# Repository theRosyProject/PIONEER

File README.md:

# PIONEER
Marie Skłodowska-Curie grant agreement No. 844526 

https://cordis.europa.eu/project/id/844526

## Publications
Dallo, Federico, et al. "Calibration and assessment of electrochemical low-cost sensors in remote alpine harsh environments." Atmospheric Measurement Techniques 14.9 (2021): 6005-6021. https://doi.org/10.5194/amt-14-6005-2021

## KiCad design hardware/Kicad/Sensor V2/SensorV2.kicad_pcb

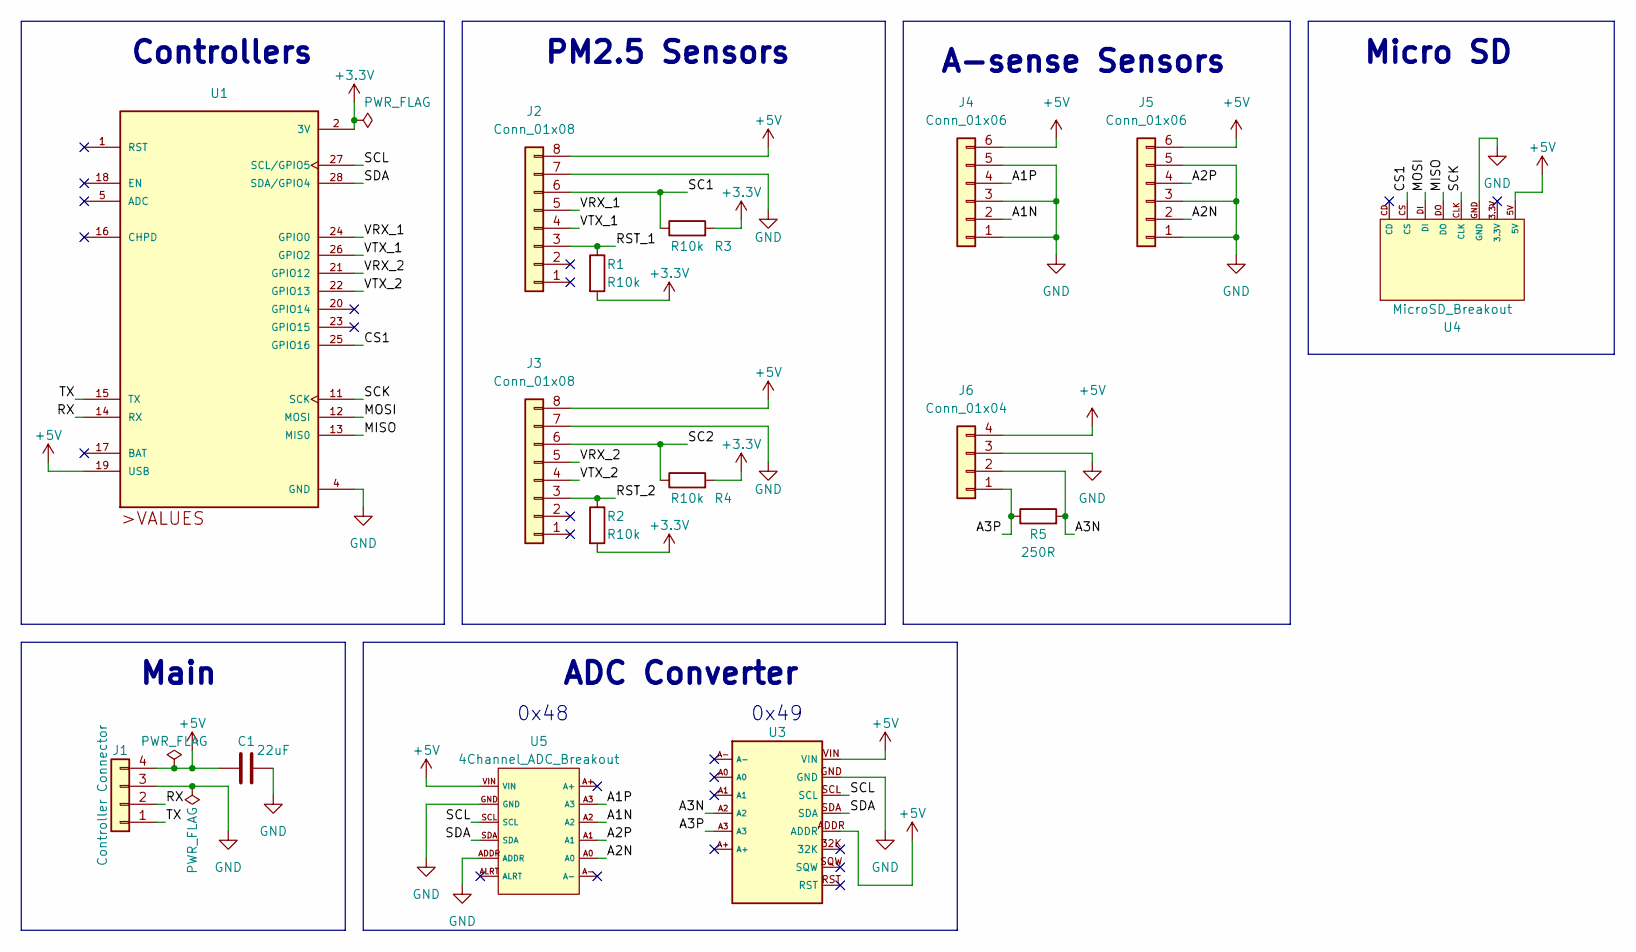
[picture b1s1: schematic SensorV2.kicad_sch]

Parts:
C1: 22uF; C_1206_3216Metric
J1: Controller Connector; PinHeader_1x04_P2.54mm_Vertical
J2, J3: Conn_01x08; Molex_CLIK-Mate_502386-0870_1x08-1MP_P1.25mm_Horizontal
J4, J5: Conn_01x06; JST_XH_B6B-XH-A_1x06_P2.50mm_Vertical
J6: Conn_01x04; JST_XH_B4B-XH-AM_1x04_P2.50mm_Vertical
R1, R2, R3, R4: R10k; R_1206_3216Metric
R5: 250R; R_0805_2012Metric
U1: 2821; XCVR_Adafruit Feather ESP8266
U3: ADCRTC_Dual
U4: MicroSD_Breakout
U5: 4Channel_ADC_Breakout; 4Channel ADC Breakout

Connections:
+3V3: R1.2, R2.2, R3.2, R4.2, U1.2 (3V)
+5V: C1.1, J1.4, J2.8, J3.8, J4.6, J5.6, J6.4, U1.19 (USB), U3.ADDR, U3.VIN, U4.5V, U5.VIN
/A1N: J4.2, U5.A2
/A1P: J4.4, U5.A3
/A2N: J5.2, U5.A0
/A2P: J5.4, U5.A1
/A3N: J6.2, R5.2, U3.A2
/A3P: J6.1, R5.1, U3.A3
/CS1: U1.25 (GPIO16), U4.CS
/MISO: U1.13 (MIS0), U4.DO
/MOSI: U1.12 (MOSI), U4.DI
/RST_1: J2.3, R1.1
/RST_2: J3.3, R2.1
/RX: J1.2, U1.14 (RX)
/SC1: J2.6, R3.1
/SC2: J3.6, R4.1
/SCK: U1.11 (SCK), U4.CLK
/SCL: U1.27 (SCL/GPIO5), U3.SCL, U5.SCL
/SDA: U1.28 (SDA/GPIO4), U3.SDA, U5.SDA
/TX: J1.1, U1.15 (TX)
/VRX_1: J2.5, U1.24 (GPIO0)
/VRX_2: J3.5, U1.21 (GPIO12)
/VTX_1: J2.4, U1.26 (GPIO2)
/VTX_2: J3.4, U1.22 (GPIO13)
GND: C1.2, J1.3, J2.7, J3.7, J4.1, J4.3, J4.5, J5.1, J5.3, J5.5, J6.3, U1.4 (GND), U3.GND, U4.GND, U5.ADDR, U5.GND

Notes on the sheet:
Controllers
ADC Converter
0x49
A-sense Sensors
Micro SD
Main
0x48
PM2.5 Sensors

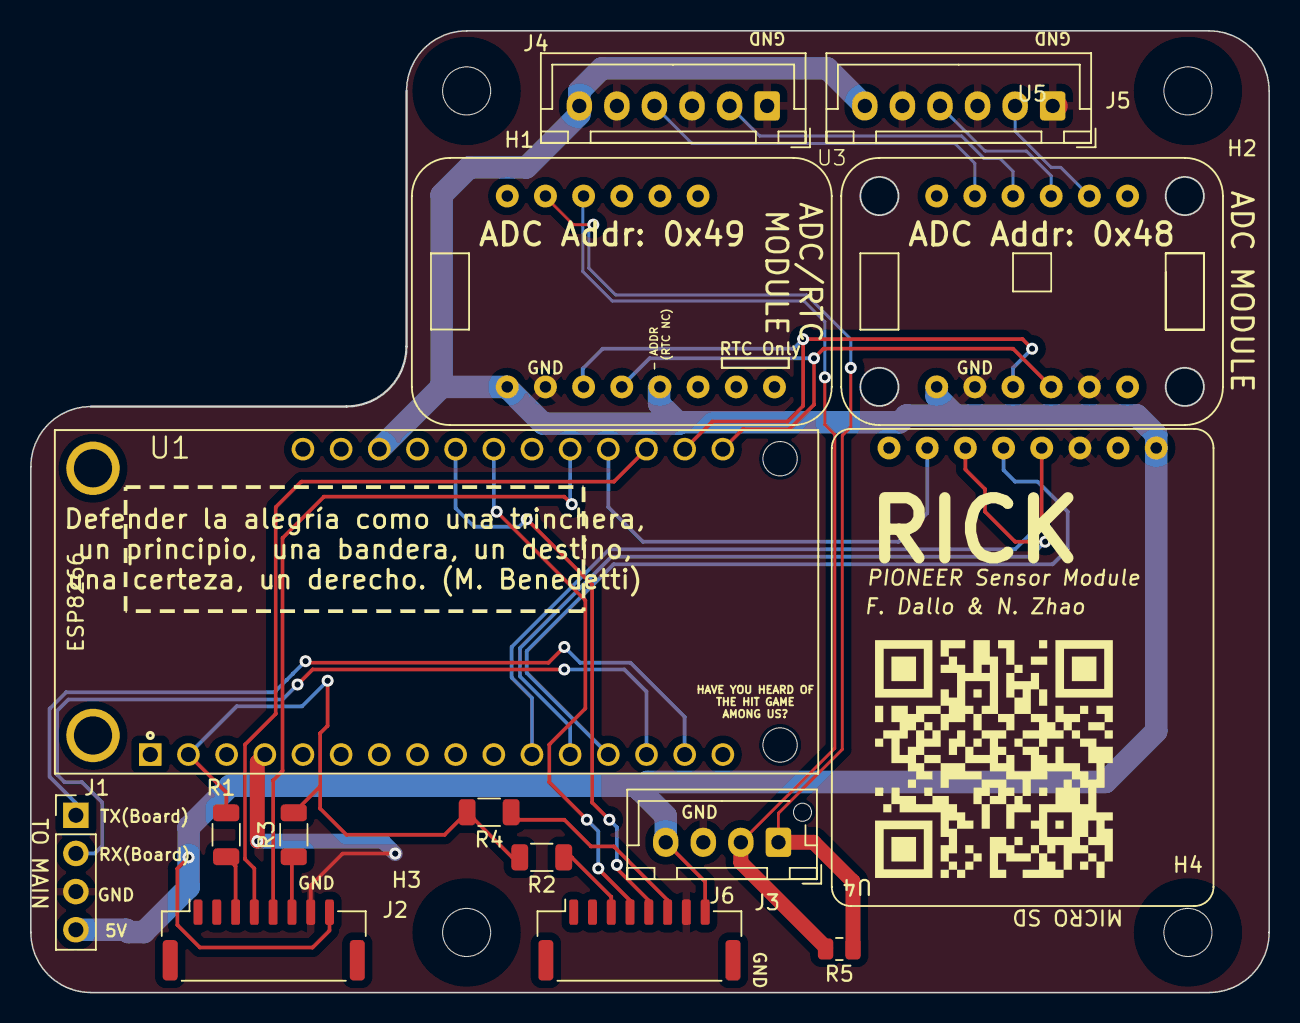
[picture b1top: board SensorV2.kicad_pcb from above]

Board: 2 copper layers, 82.4 x 64.0 mm, 20 parts (1 on the bottom side), 25 nets.

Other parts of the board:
H1, H2, H3, H4: MountingHole_3.2mm_M3

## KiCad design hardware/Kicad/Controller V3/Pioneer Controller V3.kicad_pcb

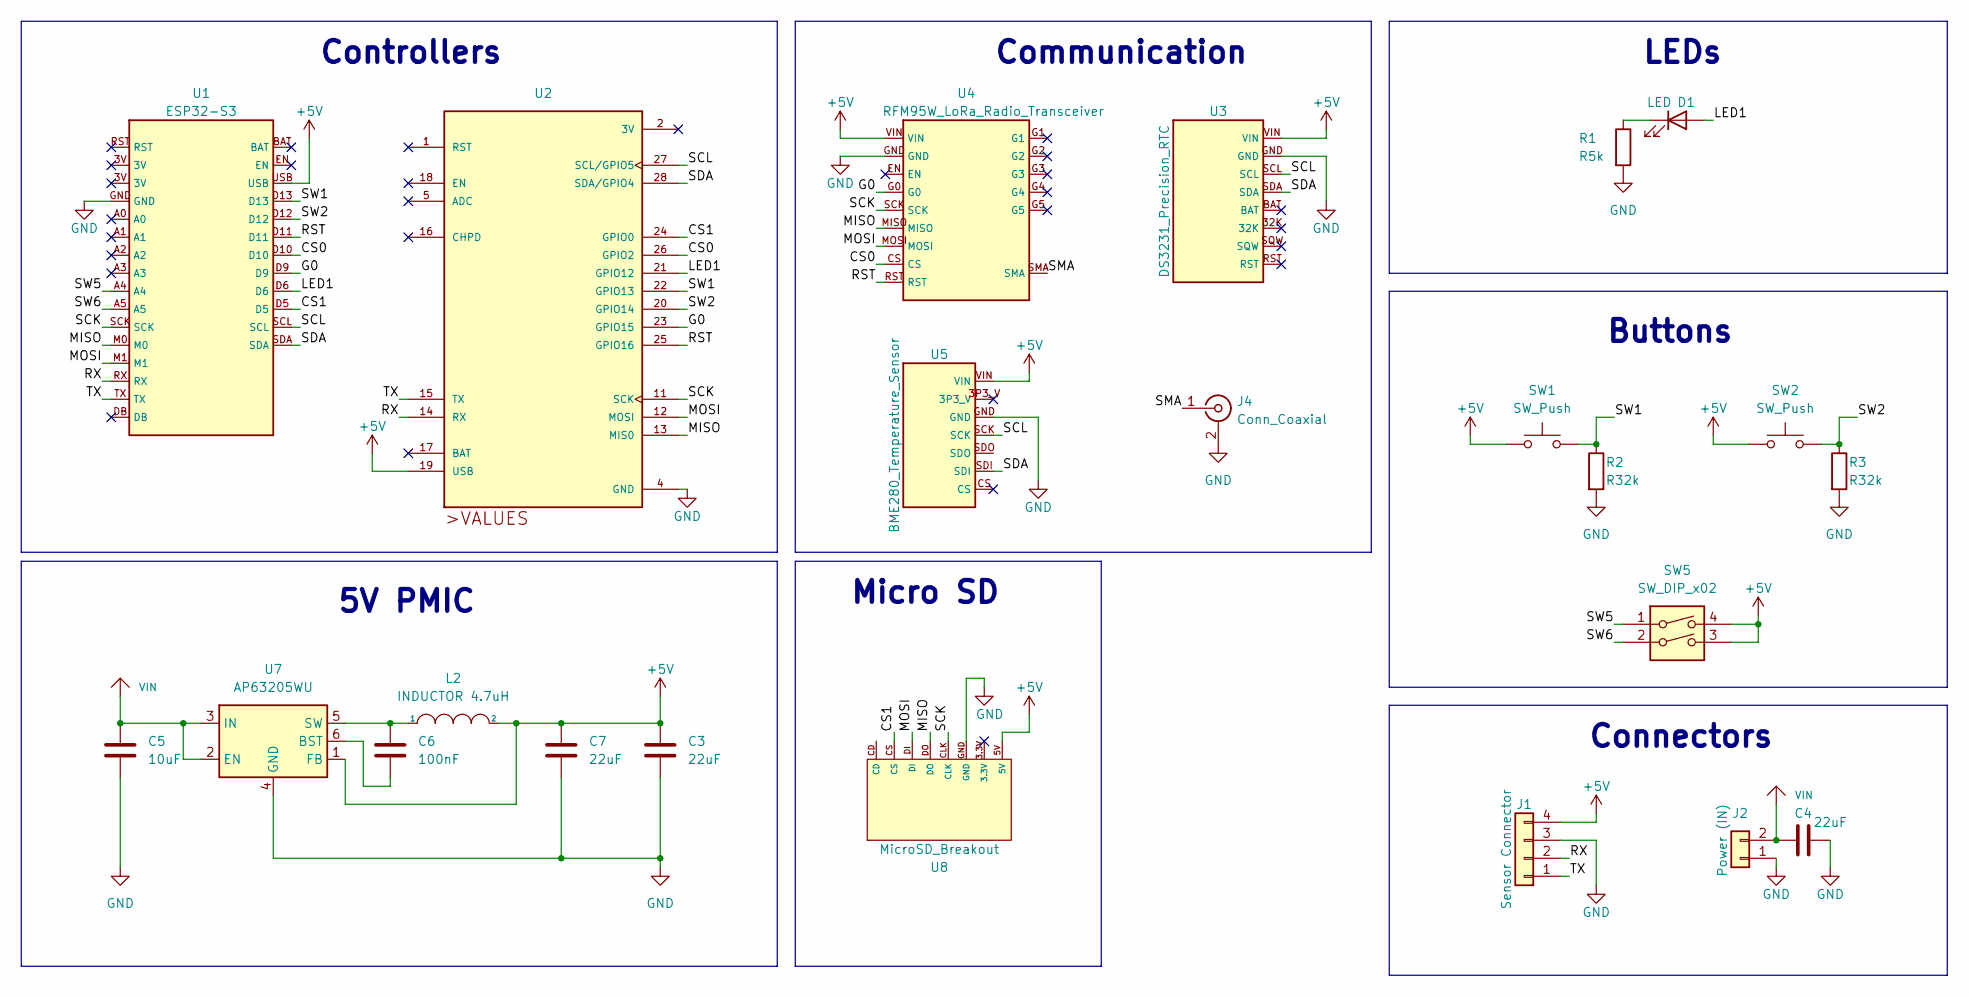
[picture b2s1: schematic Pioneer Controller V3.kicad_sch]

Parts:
C3, C4, C7: 22uF; C_1206_3216Metric
C5: 10uF; C_1206_3216Metric
C6: 100nF; C_1206_3216Metric
D1: LED; LED_1206_3216Metric
J1: Sensor Connector; PinHeader_1x04_P2.54mm_Vertical
J2: Power (IN); PinHeader_1x02_P2.54mm_Vertical
J4: Conn_Coaxial; SMA_Amphenol_132134-11_Vertical
L2: INDUCTOR 4.7uH; L_1206_3216Metric
R1: R5k; R_1206_3216Metric
R2, R3: R32k; R_1206_3216Metric
SW1, SW2: SW_Push; SW_PUSH_6mm
SW5: SW_DIP_x02; SW_DIP_SPSTx02_Slide_9.78x7.26mm_W7.62mm_P2.54mm
U1: ESP32-S3
U2: 2821; XCVR_Adafruit Feather ESP8266
U3: DS3231_Precision_RTC; DS3231 Precision RTC
U4: RFM95W_LoRa_Radio_Transceiver; FM95W LoRa Radio Transceiver
U5: BME280_Temperature_Sensor; BME280 I2C Temperature Sensor
U7: AP63205WU; TSOT-23-6
U8: MicroSD_Breakout

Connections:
+5V: C3.1, C7.1, J1.4, L2.2, SW1.1, SW2.1, SW5.3, SW5.4, U1.USB, U2.19 (USB), U3.VIN, U4.VIN, U5.VIN, U7.1 (FB), U8.5V
/CS0: U1.D10, U2.26 (GPIO2), U4.CS
/CS1: U1.D5, U2.24 (GPIO0), U8.CS
/G0: U1.D9, U2.23 (GPIO15), U4.G0
/LED1: D1.2 (A), U1.D6, U2.21 (GPIO12)
/MISO: U1.M0, U2.13 (MIS0), U4.MISO, U8.DO
/MOSI: U1.M1, U2.12 (MOSI), U4.MOSI, U8.DI
/RST: U1.D11, U2.25 (GPIO16), U4.RST
/RX: J1.2, U1.RX, U2.14 (RX)
/SCK: U1.SCK, U2.11 (SCK), U4.SCK, U8.CLK
/SCL: U1.SCL, U2.27 (SCL/GPIO5), U3.SCL, U5.SCK
/SDA: U1.SDA, U2.28 (SDA/GPIO4), U3.SDA, U5.SDI
/SMA: J4.1 (In), U4.SMA
/SW1: R2.1, SW1.2, U1.D13, U2.22 (GPIO13)
/SW2: R3.1, SW2.2, U1.D12, U2.20 (GPIO14)
/SW5: SW5.1, U1.A4
/SW6: SW5.2, U1.A5
/TX: J1.1, U1.TX, U2.15 (TX)
GND: C3.2, C4.2, C5.2, C7.2, J1.3, J2.1, J4.2 (Ext), R1.2, R2.2, R3.2, U1.GND, U2.4 (GND), U3.GND, U4.GND, U5.GND, U7.4 (GND), U8.GND
unnamed: D1.1 (K), R1.1
unnamed: C6.2, U7.6 (BST)
unnamed: C6.1, L2.1, U7.5 (SW)
VIN: C4.1, C5.1, J2.2, U7.2 (EN), U7.3 (IN)

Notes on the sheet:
Communication
Controllers
Connectors
Buttons
Micro SD
LEDs
5V PMIC

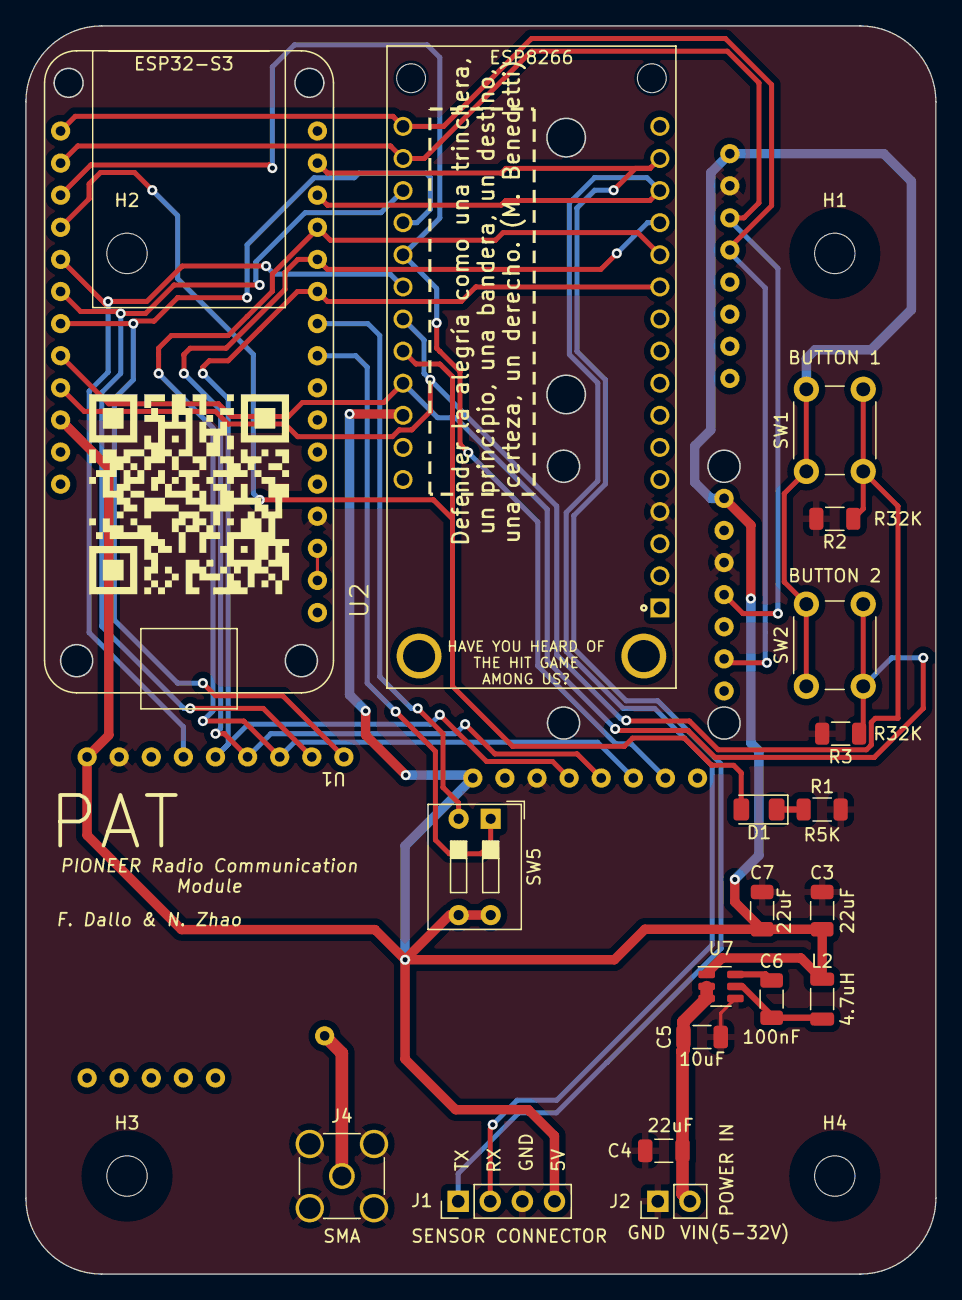
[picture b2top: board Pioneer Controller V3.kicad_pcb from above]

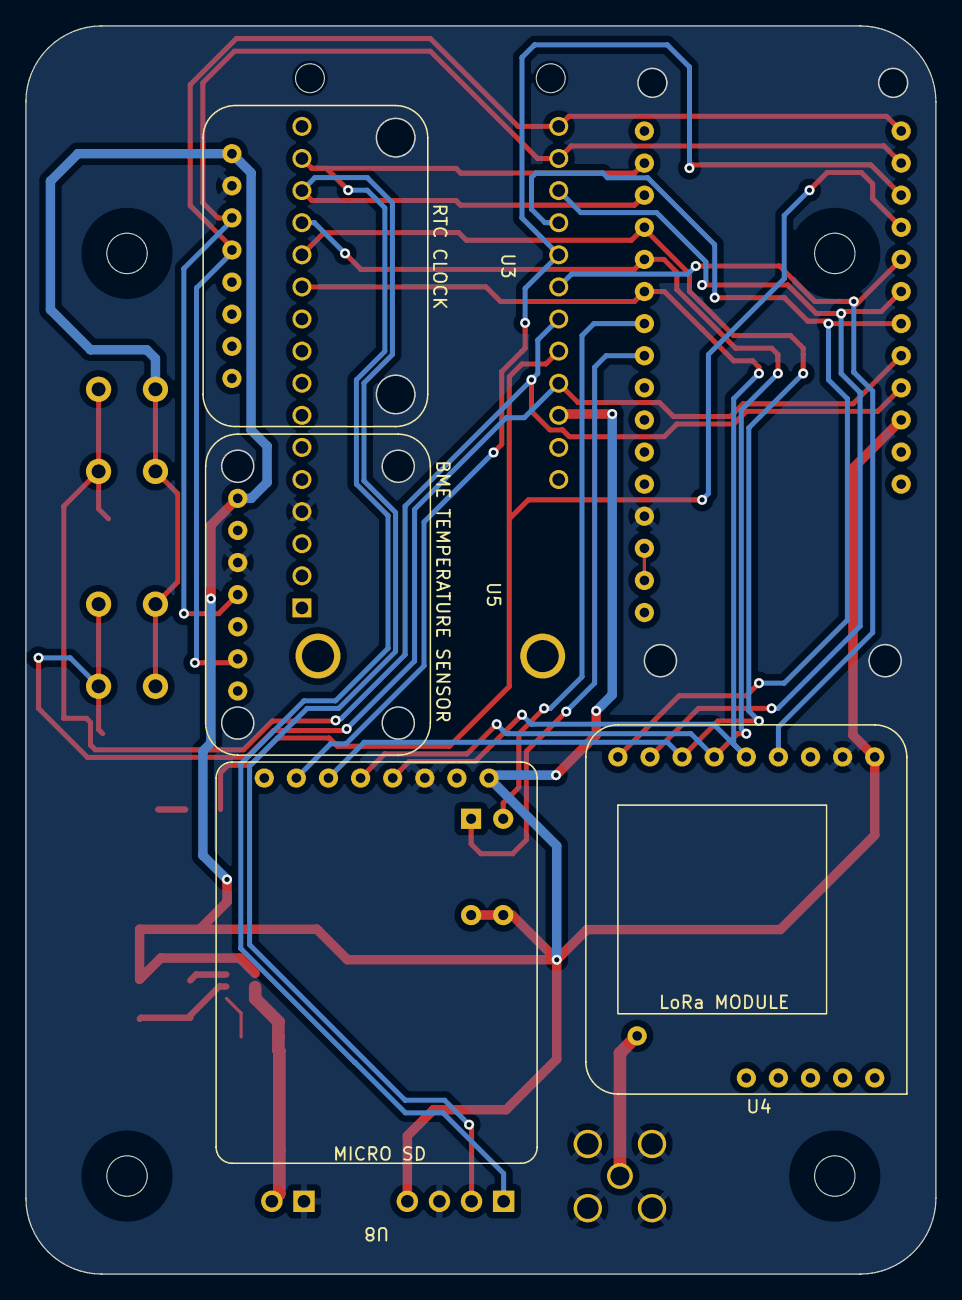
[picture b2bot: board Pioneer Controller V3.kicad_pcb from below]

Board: 2 copper layers, 72.0 x 98.7 mm, 27 parts (4 on the bottom side), 23 nets.

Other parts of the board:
H1, H2, H3, H4: MountingHole_3.2mm_M3

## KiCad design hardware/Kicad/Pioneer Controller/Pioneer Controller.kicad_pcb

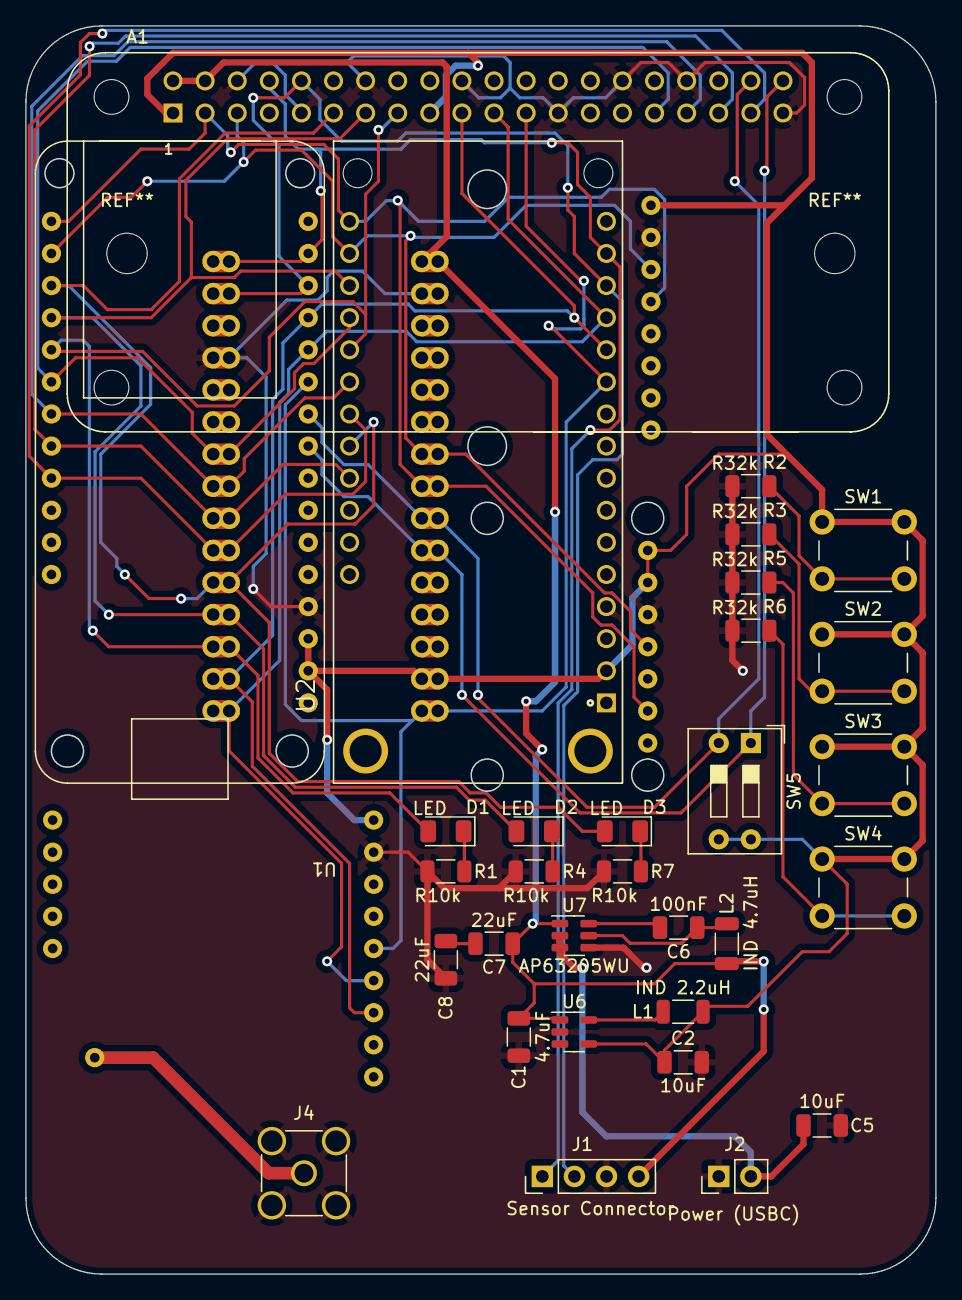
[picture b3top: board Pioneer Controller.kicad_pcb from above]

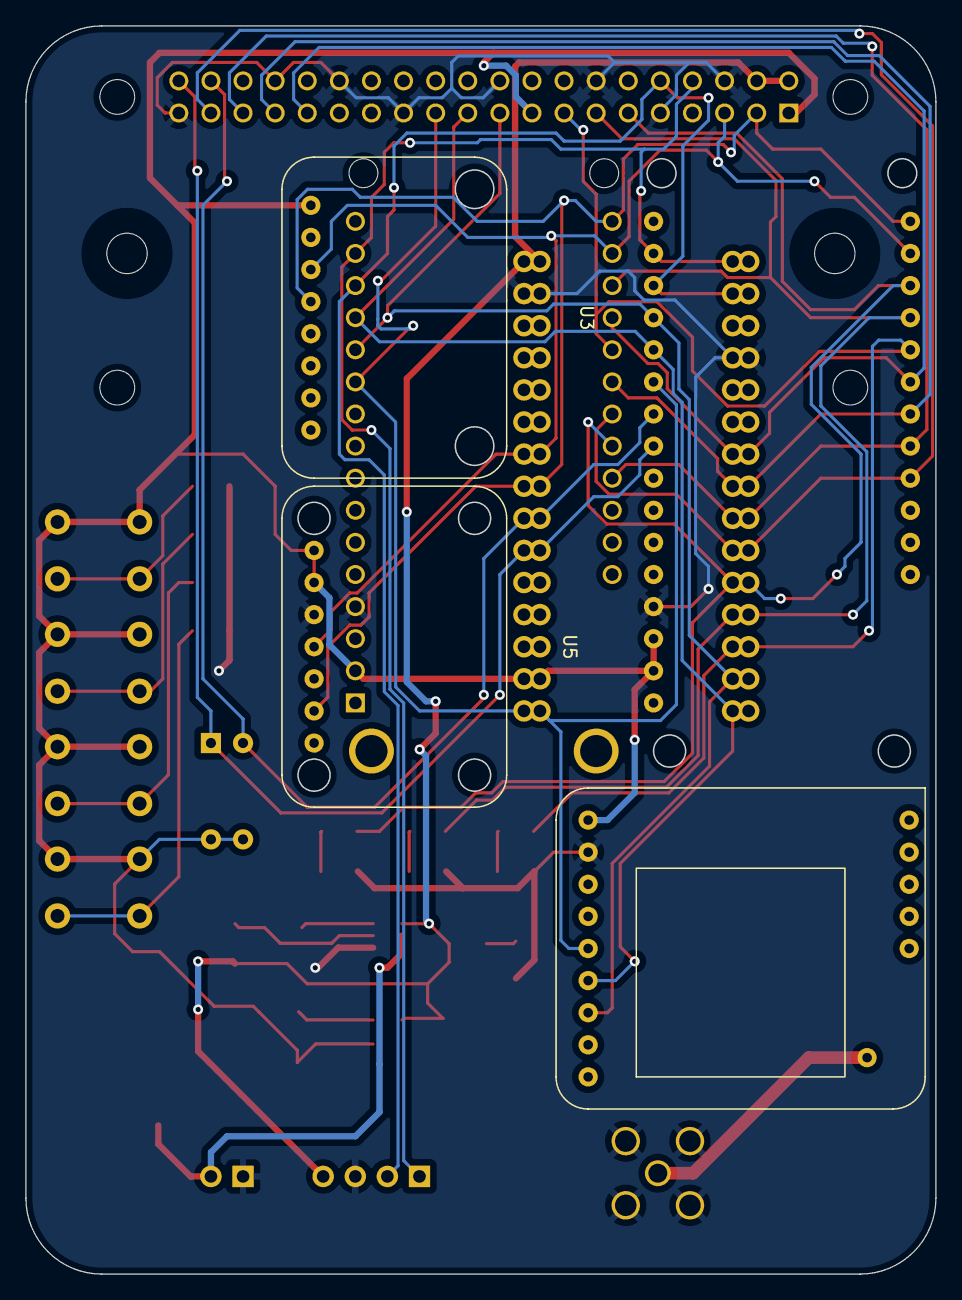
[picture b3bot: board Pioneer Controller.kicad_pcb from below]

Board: 2 copper layers, 72.0 x 98.7 mm, 35 parts (3 on the bottom side), 32 nets.

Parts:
A1: Pi-Zero; ADA3708_RPI-ZERO
C1: 4.7uF; C_1206_3216Metric
C2, C5: 10uF; C_1206_3216Metric
C6: 100nF; C_1206_3216Metric
C7, C8: 22uF; C_1206_3216Metric
D1, D2, D3: LED; LED_1206_3216Metric
J1: Sensor Connector; PinHeader_1x04_P2.54mm_Vertical
J2: Power (USBC); PinHeader_1x02_P2.54mm_Vertical
J3: Arduino-NANO-33; NANO_33_Socket_Castell
J4: Conn_Coaxial; SMA_Amphenol_132134-11_Vertical
L1: IND 2.2uH; L_1206_3216Metric
L2: IND 4.7uH; L_1206_3216Metric
R1, R4, R7: R10k; R_1206_3216Metric
R2, R3, R5, R6: R32k; R_1206_3216Metric
SW1, SW2, SW3, SW4: SW_MEC_5E; SW_PUSH_6mm
SW5: SW_DIP_x02; SW_DIP_SPSTx02_Slide_9.78x7.26mm_W7.62mm_P2.54mm
U1: ESP32-S3
U2: 2821; XCVR_Adafruit Feather ESP8266
U3: DS3231_Precision_RTC; DS3231 Precision RTC
U4: RFM95W_LoRa_Radio_Transceiver; FM95W LoRa Radio Transceiver
U5: BME280_Temperature_Sensor; BME280 I2C Temperature Sensor
U6: LM3670MF; TSOT-23-5
U7: AP63205WU; TSOT-23-6

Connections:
+3V3: A1.1 (3V3[1]), A1.17 (3V3[2]), C2.1, J3.2, L1.2, SW1.1, SW2.1, SW3.1, SW4.1, SW5.3, SW5.4, U1.3V, U2.2 (3V), U3.VIN, U4.VIN, U5.3P3_V, U5.VIN, U6.4 (FB)
+5V: A1.2 (5V[1]), A1.4 (5V[2]), C1.1, C7.1, J1.4, J3.15, L2.2, U6.1 (Vin), U7.1 (FB)
/LED1: A1.15 (GPIO22/GEN3), D1.2 (A), J3.28, U1.D9, U2.24 (GPIO0)
/LED2: A1.13 (GPIO27/GEN2), D2.2 (A), J3.27, U1.D6, U2.26 (GPIO2)
/LED3: A1.11 (GPIO17/GEN0), D3.2 (A), J3.26, U1.D5, U2.21 (GPIO12)
/MISO: A1.21 (GPIO9/MISO), J3.30, U1.M0, U2.13 (MIS0), U4.MISO
/MOSI: A1.19 (GPIO10/MOSI), J3.29, U1.M1, U2.12 (MOSI), U4.MOSI
/RX: A1.10 (RXD0/GPIO15), J1.2, J3.17, U1.RX, U2.14 (RX)
/SCK: A1.23 (GPIO11/SCLK), J3.1, U1.SCK, U2.11 (SCK), U4.SCK
/SCL: A1.5 (GPIO3/SCL), J3.9, U1.SCL, U2.27 (SCL/GPIO5), U3.SCL, U5.SCK
/SDA: A1.3 (GPIO2/SDA), J3.8, U1.SDA, U2.28 (SDA/GPIO4), U3.SDA, U5.SDI
/SMA: J4.1 (In), U4.SMA
/SW1: A1.37 (GPIO26), J3.25, U1.D13, U2.22 (GPIO13)
/SW2: A1.35 (GPIO19), J3.24, U1.D12, U2.20 (GPIO14)
/SW3: A1.33 (GPIO13), J3.23, U1.D11, U2.23 (GPIO15)
/SW4: A1.31 (GPIO6), J3.22, U1.D10, U2.25 (GPIO16)
/SW5: A1.40 (GPIO21), J3.6, SW5.1, U1.A4
/SW6: A1.38 (GPIO20), J3.7, SW5.2, U1.A5
/TX: A1.8 (TXD0/GPIO14), J1.1, J3.16, U1.TX, U2.15 (TX)
GND: A1.6 (GND[8]), A1.9 (GND[1]), A1.14 (GND[4]), A1.20 (GND[5]), A1.25 (GND[2]), A1.30 (GND[6]), A1.34 (GND[7]), A1.39 (GND[3]), C1.2, C2.2, C5.2, C8.2, J1.3, J2.1, J3.14, J3.19, J4.2 (Ext), R1.2, R2.2, R3.2, R4.2, R5.2, R6.2, R7.2, U1.GND, U2.4 (GND), U3.GND, U4.GND, U5.GND, U6.2 (GND), U7.4 (GND)
unnamed: C6.1, L2.1, U7.5 (SW)
unnamed: C6.2, U7.6 (BST)
unnamed: C7.2, C8.1
unnamed: D1.1 (K), R1.1
unnamed: D2.1 (K), R4.1
unnamed: D3.1 (K), R7.1
unnamed: L1.1, U6.5 (SW)
unnamed: R2.1, SW1.2
unnamed: R3.1, SW2.2
unnamed: R5.1, SW3.2
unnamed: R6.1, SW4.2
VIN: C5.1, J2.2, U7.2 (EN), U7.3 (IN)

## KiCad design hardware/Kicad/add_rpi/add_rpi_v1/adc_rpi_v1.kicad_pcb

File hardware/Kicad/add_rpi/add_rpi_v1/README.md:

Schematics for interface 4 analog sensors with the Raspberry Pi Zero W via i2c.

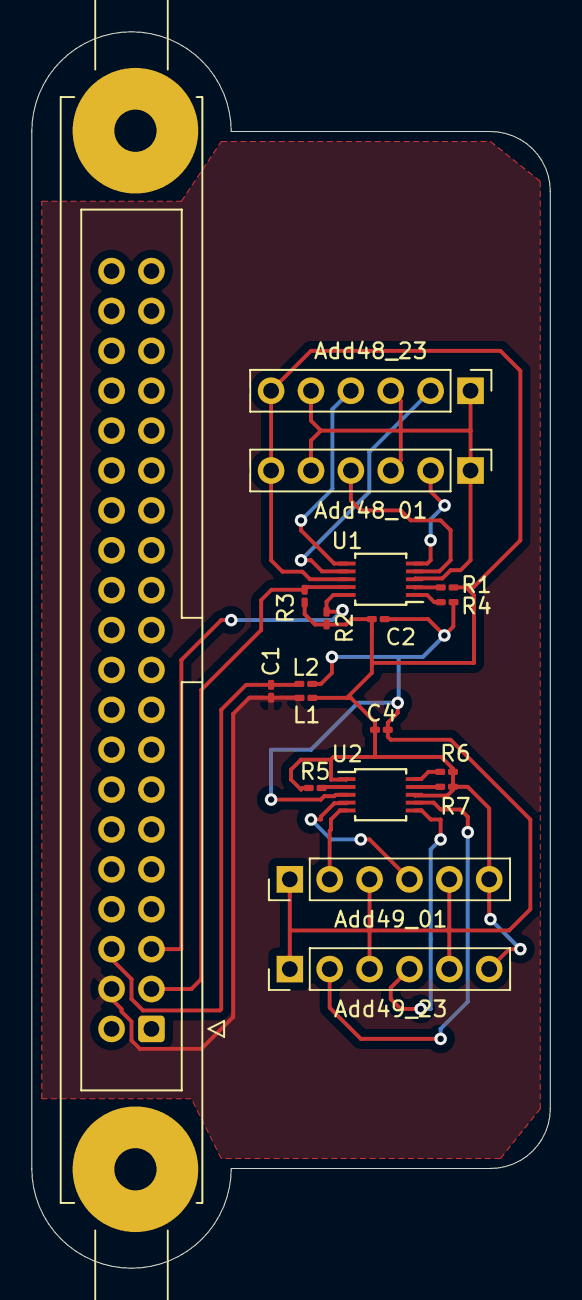
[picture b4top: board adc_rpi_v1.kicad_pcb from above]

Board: 2 copper layers, 33.0 x 78.7 mm, 19 parts (0 on the bottom side), 14 nets.

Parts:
Add48_01: Sensor 1; PinHeader_1x06_P2.54mm_Vertical
Add48_23: Sensor 2; PinHeader_1x06_P2.54mm_Vertical
Add49_01: Sensor 3; PinHeader_1x06_P2.54mm_Vertical
Add49_23: Sensor 4; PinHeader_1x06_P2.54mm_Vertical
C1, C2, C4: 1uF; C_0201_0603Metric_Pad0.64x0.40mm_HandSolder
J1: Conn_02x20_Odd_Even_MountingPin; IDC-Header_2x20-1MP_P2.54mm_Latch6.5mm_Vertical
L1, L2: INDUCTOR; L_0201_0603Metric_Pad0.64x0.40mm_HandSolder
R1, R2, R3, R4, R5, R6, R7: 10k; R_0201_0603Metric_Pad0.64x0.40mm_HandSolder
U1, U2: ADS1115IDGS; TSSOP-10_3x3mm_P0.5mm

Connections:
+5V: Add48_01.6, Add48_23.6, Add49_01.6, Add49_23.6, C2.1, C4.1, L1.2, R1.1, R2.1, R3.1, R5.1, R6.1, R7.1, U1.8, U2.1, U2.8
ALERT: R1.2, R5.2, U1.2, U2.2
GND: Add48_01.1, Add48_01.3, Add48_01.5, Add48_23.1, Add48_23.3, Add48_23.5, Add49_01.1, Add49_01.3, Add49_01.5, Add49_23.1, Add49_23.3, Add49_23.5, C1.1, C2.2, C4.2, J1.6, L2.1, L2.2, R4.1, R4.2, U1.1, U1.3, U2.3
S1_AUX+: Add48_01.2, U1.5
S1_WE+: Add48_01.4, U1.4
S2_AUX+: Add48_23.2, U1.7
S2_WE+: Add48_23.4, U1.6
S3_AUX+: Add49_01.2, U2.5
S3_WE+: Add49_01.4, U2.4
S4_AUX+: Add49_23.2, U2.7
S4_WE+: Add49_23.4, U2.6
SCL: J1.5, R2.2, R6.2, U1.10, U2.10
SDA: J1.3, R3.2, R7.2, U1.9, U2.9
VDD: C1.2, J1.4, L1.1

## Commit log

2021-05-04 Rename msg to LoRa/msg
2021-05-15 Create file
2022-09-19 fix: reordering the repository
2022-09-19 feat: adding list of modules for box 1 data communication
2022-09-19 fix: adding documentation for ESP32
2022-09-26 finished schematic
2022-09-27 fix: ingnore apple local files
2022-09-27 fix: adding infos on antenna. adding log of meeting
2022-09-27 fix: adding the connector for the PCB
2022-09-27 fix: adding the com box specs
2022-10-02 did some 3D model stuff
2022-10-02 bruh
2022-10-02 finished first PCB draft
2022-10-02 test 3d file format 2
2022-10-02 pain
2022-10-02 3d model tet 3
2022-10-04 feat: adding link to power and data connector
2022-10-08 PCB 3D model
2022-10-08 some more 3D model changes
2022-10-09 temp stuff
2022-10-09 stuff
2022-10-10 more 3D modelling stuff
2022-10-10 more PCb updates
2022-10-10 more 3D model updates
2022-10-13 updated 3.3V PMIC
2022-10-15 updated 3D model
2022-10-15 poggers
2022-10-25 fix: orders submitted
2022-11-04 fix: adding docs
2022-11-06 fix: adding orders
2022-11-17 feat: reordering the filesystem considering the project structure reported here: https://drivendata.github.io/cookiecutter-data-science/
2022-11-22 soft and pins connections between ESP8266 and LoRa
2022-11-28 did more stuff for sensor box
2022-11-28 bruh fetch pain
2022-12-05 feat: adding functionalities on the LoRa Gateway
2022-12-06 adding TX program functionality to send message received by serial com
2022-12-07 fix: now sending packet only if serial message is complete
2022-12-13 feat: adding the first version of working AP on ESP8266
2022-12-23 stuff 2
2022-12-28 started main controller V2
2023-01-05 finished sensor PCB
2023-01-13 small pcb changes
2023-01-13 added PCB model
2023-01-14 updated PCBS
2023-01-14 updated PCB labels
2023-01-17 added extra resistor
2023-01-18 feat: base code for the SD card saving
2023-03-03 updated 3D models
2023-03-19 feat: creating the code for the Svalbard test that Daniele will perform on April/May 2023. The code is in the software directory under fieldwork
2023-03-19 feat: adding broker and logging script configuration for the Svalbard experiment
2023-03-28 feat: suggestions for finalize the PCBs
2023-03-28 fix: adding notes
2023-03-28 fix: fixing the todo list
2023-03-31 updated footptint
2023-04-07 feat: adding software
2023-04-11 fixed CS to gpio16
2023-04-12 feat: adding new software
2023-04-12 fix: had to add to repo
2023-04-18 updated PCB
2023-04-19 updated 5v
2023-04-20 feat: adding qr code for the project and manual for the pinout of esp32
2023-04-21 feat: adding pictures about the fieldwork at Svalbard on April 2023
2023-04-22 added some changes
2023-04-24 feat: last kicad updates before sending order
2023-04-26 feat: adding software, home assistant and esphome configuration
